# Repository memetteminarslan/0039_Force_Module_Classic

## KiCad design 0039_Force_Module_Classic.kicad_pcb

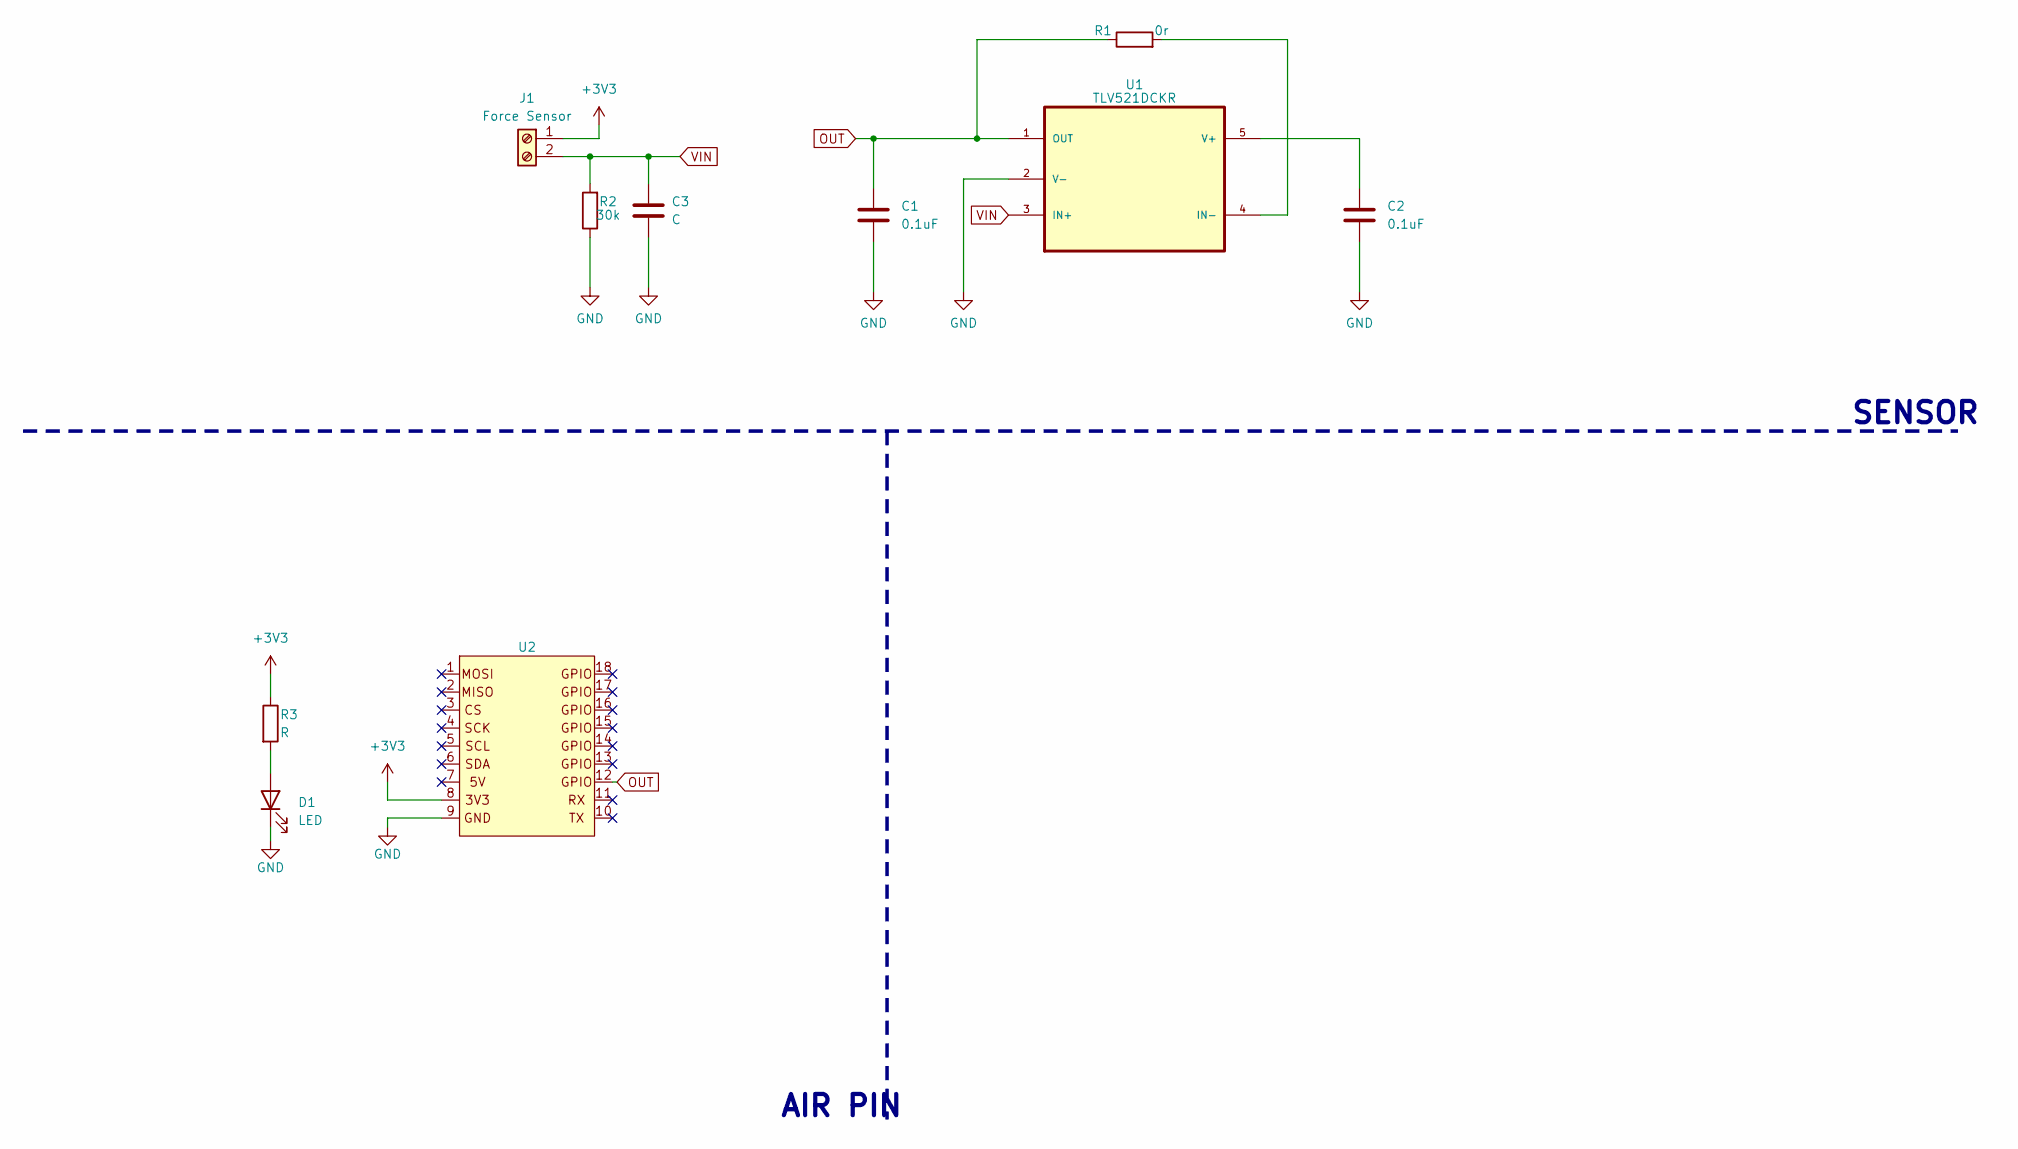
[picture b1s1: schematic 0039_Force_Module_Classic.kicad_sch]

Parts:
C1, C2: 0.1uF; C_0805_2012Metric
C3: C; C_0805_2012Metric
D1: LED; LED_0805_2012Metric
J1: Force Sensor; TerminalBlock_Phoenix_MPT-0,5-2-2.54_1x02_P2.54mm_Horizontal
R1: 0r; R_0805_2012Metric
R2: 30k; R_0805_2012Metric
R3: R; R_0805_2012Metric
U1: TLV521DCKR; SOT65P210X110-5N
U2: pin_header

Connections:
+3V3: J1.1, R3.1, U2.8
GND: C1.2, C2.2, C3.2, D1.1 (K), R2.1, U1.2 (V-), U2.9
unnamed: D1.2 (A), R3.2
unnamed: R1.2, U1.4 (IN-)
unnamed: C2.1, U1.5 (V+)
OUT: C1.1, R1.1, U1.1 (OUT), U2.12
VIN: C3.1, J1.2, R2.2, U1.3 (IN+)

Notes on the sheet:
AIR PIN
SENSOR

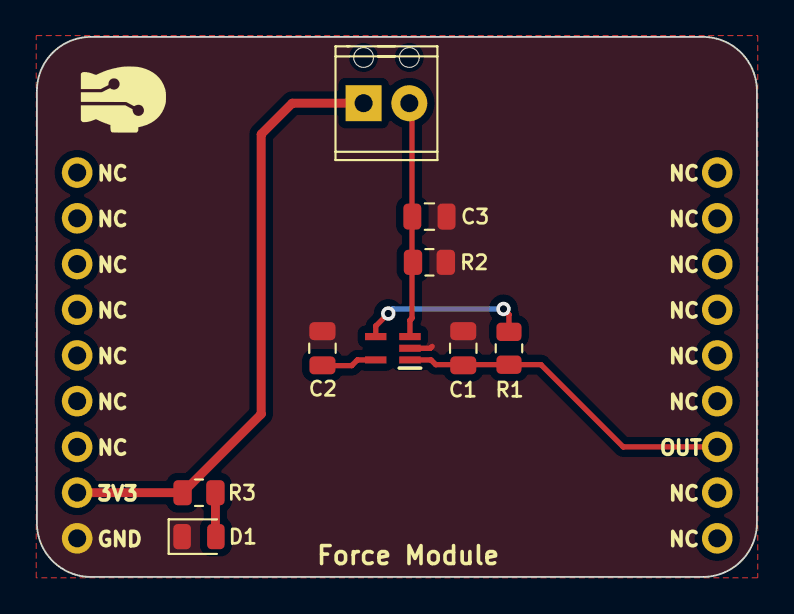
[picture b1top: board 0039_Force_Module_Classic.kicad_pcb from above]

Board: 2 copper layers, 40.0 x 30.0 mm, 10 parts (0 on the bottom side), 7 nets.
